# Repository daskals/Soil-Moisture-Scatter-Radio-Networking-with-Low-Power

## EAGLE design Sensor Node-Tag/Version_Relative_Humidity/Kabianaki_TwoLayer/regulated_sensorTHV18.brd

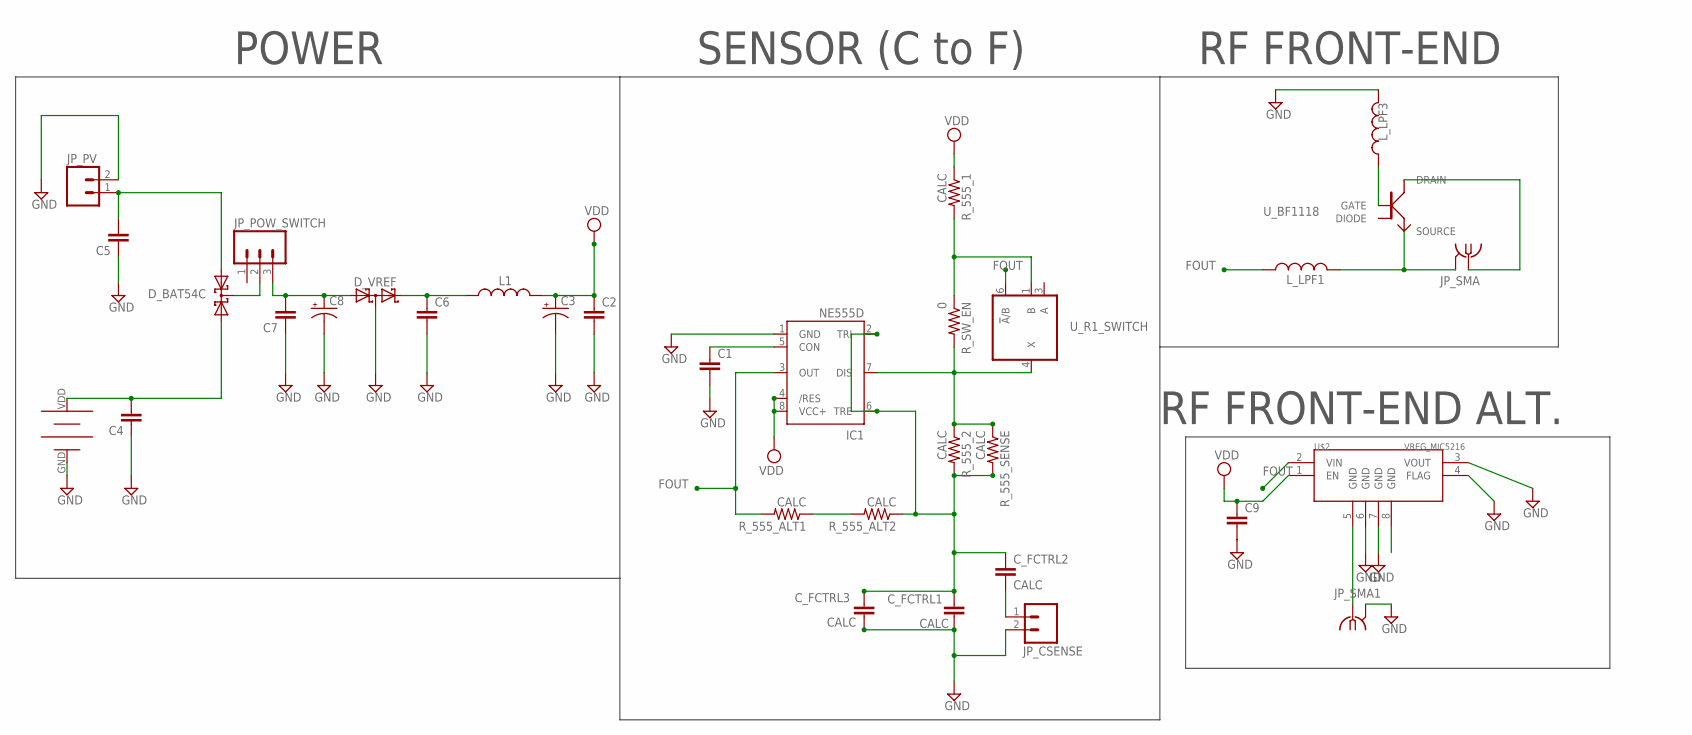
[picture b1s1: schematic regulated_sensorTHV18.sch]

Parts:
C1, C2, C4, C5, C6, C7, C9: CAP0603-CAP; 0603-CAP
C3, C8: CAP_POL1206; EIA3216
C_FCTRL1, C_FCTRL2, C_FCTRL3: CALC; 0603-CAP
D_BAT54C: BAT54C; SOT23
D_VREF: BAT54S; SOT23
IC1: NE555D; SO08
JP_CSENSE: M02LOCK; 1X02_LOCK
JP_POW_SWITCH: M03LOCK; 1X03_LOCK
JP_PV: M02LOCK; 1X02_LOCK
JP_SMA, JP_SMA1: SMA-142-0701-881/886; J502-ND-142-0701-881/886
L1: INDUCTOR0603; 0603
L_LPF1, L_LPF3: INDUCTOR0603; 0603
R_555_1: CALC; 0805
R_555_2, R_555_ALT1, R_555_ALT2, R_555_SENSE: CALC; 0603-RES
R_SW_EN: 0; 0805
U$1: BATTERY_AAA_EAGLE_PLASTIC_DEVICES_DOUBLE; BATTERY-AAA-50MM-DOUBLE
U$2: VREG_MIC5216; MSOP8
U_BF1118: BF1118SOT343R_NXP; SOT343R
U_R1_SWITCH: 741G3157DCKR; DCK_R-PDSO-G6

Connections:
FOUT: IC1.3 (OUT), L_LPF1.1, R_555_ALT1.2, U$2.2 (VIN), U_R1_SWITCH.6 (!A!/B)
GND: C1.2, C2.2, C3.C (-), C4.1, C5.1, C6.2, C7.1, C8.C (-), C9.2, C_FCTRL1.2, C_FCTRL3.2, D_VREF.3 (C1A2), IC1.1 (GND), JP_CSENSE.2, JP_PV.2, JP_SMA1.G@1 (2), JP_SMA1.G@2 (2), JP_SMA1.G@3 (2), JP_SMA1.G@4 (2), L_LPF3.2, U$1.GND, U$2.3 (VOUT), U$2.4 (FLAG), U$2.6 (GND), U$2.7 (GND), U_R1_SWITCH.2 (GND)
unnamed: C5.2, D_BAT54C.1 (A1), JP_PV.1
unnamed: C7.2, C8.A (+), D_VREF.1 (A1), JP_POW_SWITCH.3
unnamed: D_BAT54C.3 (CC), JP_POW_SWITCH.2
unnamed: L_LPF3.1, U_BF1118.1 (GATE)
unnamed: C6.1, D_VREF.2 (C2), L1.1
unnamed: C_FCTRL1.1, C_FCTRL2.1, C_FCTRL3.1, IC1.2 (TRI), IC1.6 (TRE), R_555_2.2, R_555_ALT2.1, R_555_SENSE.2
unnamed: C_FCTRL2.2, JP_CSENSE.1
unnamed: R_555_1.2, R_SW_EN.1, U_R1_SWITCH.1 (B)
unnamed: C1.1, IC1.5 (CON)
unnamed: IC1.7 (DIS), R_555_2.1, R_555_SENSE.1, R_SW_EN.2, U_R1_SWITCH.4 (X)
unnamed: JP_SMA1.1, U$2.5 (GND)
unnamed: C4.2, D_BAT54C.2 (A2), U$1.VDD
unnamed: R_555_ALT1.1, R_555_ALT2.2
RF_FEEDBACK: JP_SMA.G@1 (2), JP_SMA.G@2 (2), JP_SMA.G@3 (2), JP_SMA.G@4 (2), L_LPF1.2, U_BF1118.3 (SOURCE)
RF_IN: JP_SMA.1, U_BF1118.4 (DRAIN)
VDD: C2.1, C3.A (+), C9.1, IC1.4 (/RES), IC1.8 (VCC+), L1.2, R_555_1.1, U$2.1 (EN), U_R1_SWITCH.5 (VCC)

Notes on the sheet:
POWER
SENSOR (C to F)
RF FRONT-END
RF FRONT-END ALT.

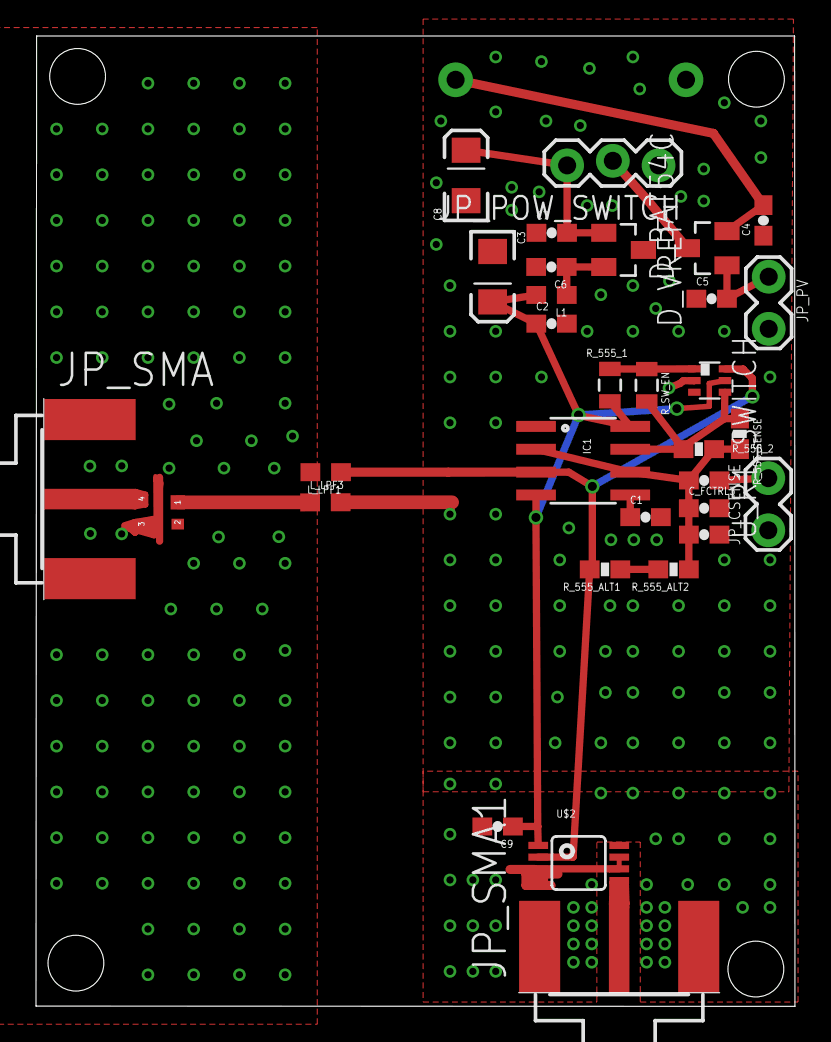
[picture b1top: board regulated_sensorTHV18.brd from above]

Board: 2 copper layers, 42.2 x 53.9 mm, 33 parts (1 on the bottom side), 18 nets.

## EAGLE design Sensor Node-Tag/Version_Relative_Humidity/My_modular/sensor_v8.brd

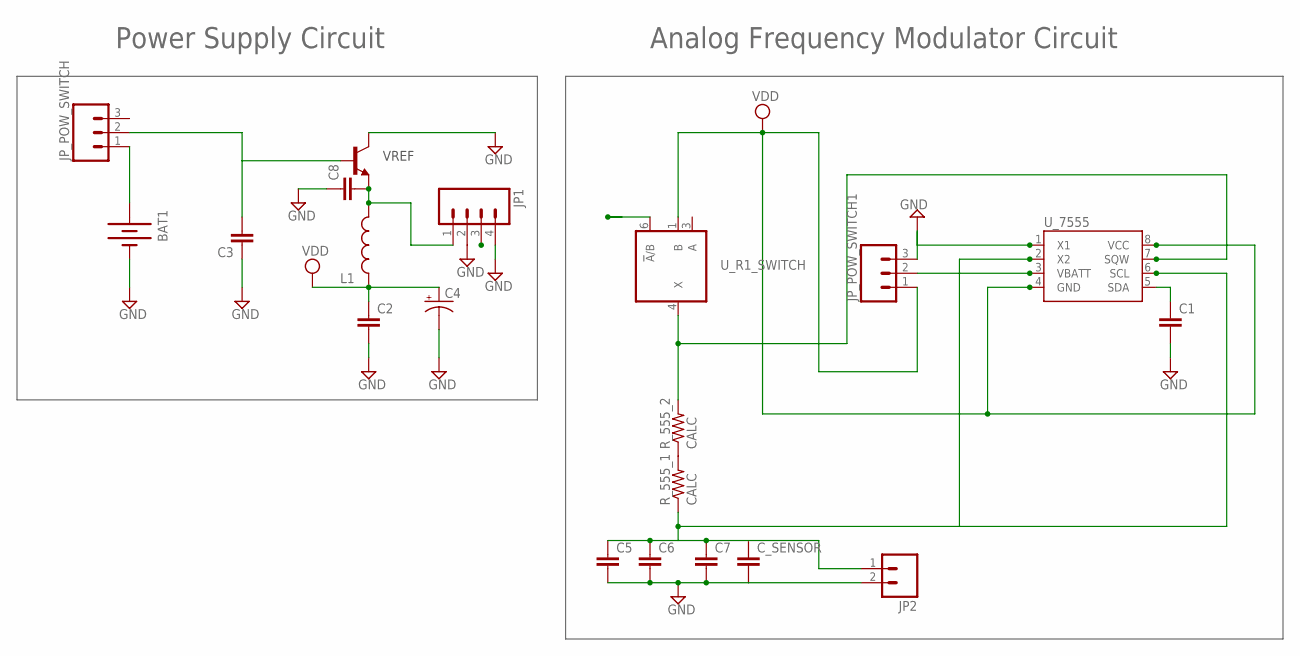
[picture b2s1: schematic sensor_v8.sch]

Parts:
BAT1: BATTERY20PTH_LAB; BATTCOM_20MM_PTH
C1, C2, C3, C8: CAP0603-CAP; 0603-CAP
C4: CAP_POL1206; EIA3216
C5, C6, C7: CAP0805; 0805
C_SENSOR: CAP0805; 0805
JP1: M04LOCK; 1X04_LOCK
JP2: M02PTH; 1X02
JP_POW_SWITCH, JP_POW_SWITCH1: M03LOCK; 1X03_LOCK
L1: INDUCTOR0603; 0603
R_555_1, R_555_2: CALC; 0805
U_7555: DS1307SO8; SO08
U_R1_SWITCH: 741G3157DCKR; DCK_R-PDSO-G6
U_VREF: TRANSISTOR_NPNSOT23-3; SOT23-3

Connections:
FOUT: JP_POW_SWITCH1.2, U_7555.3 (VBATT), U_R1_SWITCH.6 (!A!/B)
GND: BAT1.2 (-), C1.2, C2.2, C3.1, C4.C (-), C5.2, C6.2, C7.2, C8.1, C_SENSOR.2, JP1.2, JP1.4, JP2.2, JP_POW_SWITCH1.3, U_7555.1 (X1), U_R1_SWITCH.2 (GND), U_VREF.3 (C)
unnamed: BAT1.1 (+), JP1.3, JP_POW_SWITCH.1
unnamed: R_555_1.2, R_555_2.1
P2: C5.1, C6.1, C7.1, C_SENSOR.1, JP2.1, R_555_1.1, U_7555.2 (X2), U_7555.6 (SCL)
P5: C1.1, U_7555.5 (SDA)
P7: R_555_2.2, U_7555.7 (SQW), U_R1_SWITCH.4 (X)
VCC: U_R1_SWITCH.5 (VCC)
VDD: C2.1, C4.A (+), JP_POW_SWITCH1.1, L1.1, U_7555.4 (GND), U_7555.8 (VCC), U_R1_SWITCH.1 (B)
VREFIN: C3.2, JP_POW_SWITCH.2, U_VREF.1 (B)
VREFOUT: C8.2, JP1.1, L1.2, U_VREF.2 (E)

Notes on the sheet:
Power Supply Circuit
Analog Frequency Modulator Circuit
VREF

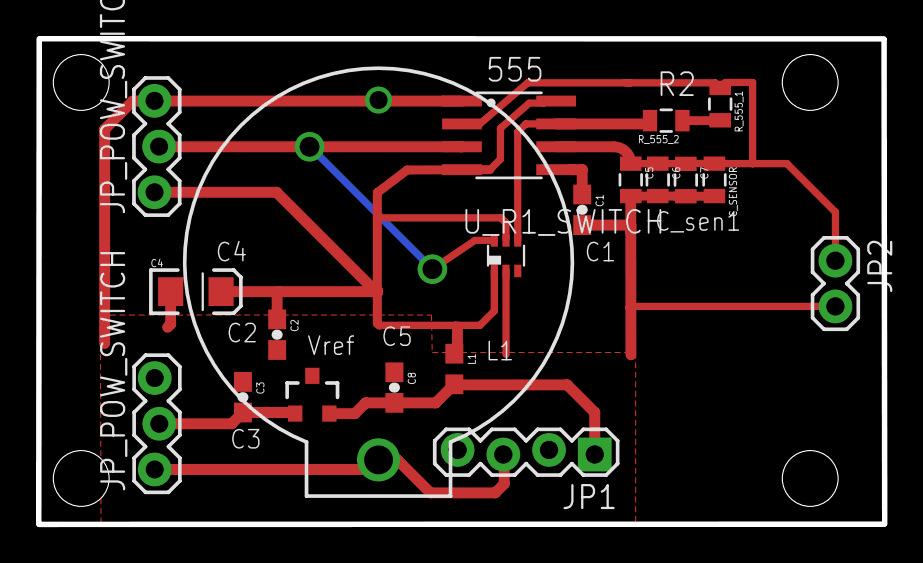
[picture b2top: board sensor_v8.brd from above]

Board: 2 copper layers, 47.0 x 27.0 mm, 20 parts (0 on the bottom side), 10 nets.

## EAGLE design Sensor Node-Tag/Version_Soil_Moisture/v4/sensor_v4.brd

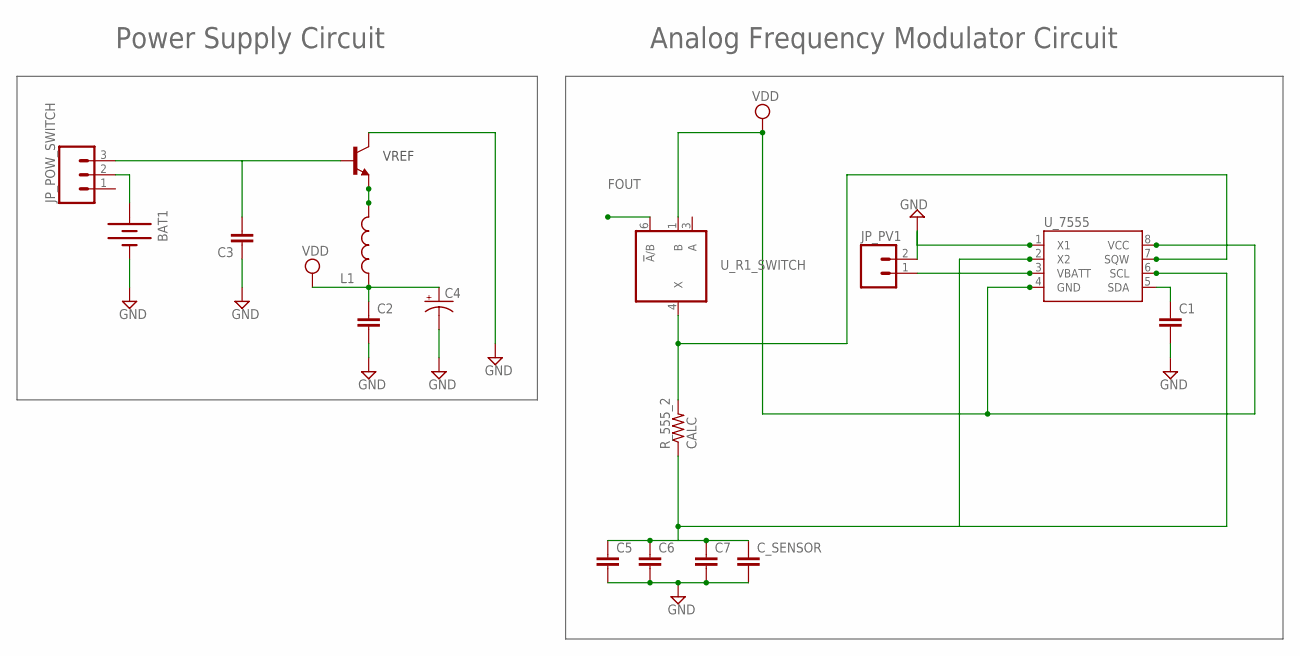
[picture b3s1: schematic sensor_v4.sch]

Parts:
BAT1: BATTERY20PTH_LAB; BATTCOM_20MM_PTH
C1, C2, C3: CAP0603-CAP; 0603-CAP
C4: CAP_POL1206; EIA3216
C5, C6, C7: CAP0805; 0805
C_SENSOR: CAP0805; 0805
JP_POW_SWITCH: M03LOCK; 1X03_LOCK
JP_PV1: M02LOCK; 1X02_LOCK
L1: INDUCTOR0603; 0603
R_555_2: CALC; 0805
U_7555: DS1307SO8; SO08
U_R1_SWITCH: 741G3157DCKR; DCK_R-PDSO-G6
U_VREF: TRANSISTOR_NPNSOT23-3; SOT23-3

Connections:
FOUT: JP_PV1.1, U_7555.3 (VBATT), U_R1_SWITCH.6 (!A!/B)
GND: BAT1.2 (-), C1.2, C2.2, C3.1, C4.C (-), C5.2, C6.2, C7.2, C_SENSOR.2, JP_PV1.2, U_7555.1 (X1), U_R1_SWITCH.2 (GND), U_VREF.3 (C)
unnamed: BAT1.1 (+), JP_POW_SWITCH.2
P2: C5.1, C6.1, C7.1, C_SENSOR.1, R_555_2.1, U_7555.2 (X2), U_7555.6 (SCL)
P5: C1.1, U_7555.5 (SDA)
P7: R_555_2.2, U_7555.7 (SQW), U_R1_SWITCH.4 (X)
VCC: U_R1_SWITCH.5 (VCC)
VDD: C2.1, C4.A (+), L1.1, U_7555.4 (GND), U_7555.8 (VCC), U_R1_SWITCH.1 (B)
VREFIN: C3.2, JP_POW_SWITCH.3, U_VREF.1 (B)
VREFOUT: L1.2, U_VREF.2 (E)

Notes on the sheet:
Power Supply Circuit
Analog Frequency Modulator Circuit
VREF

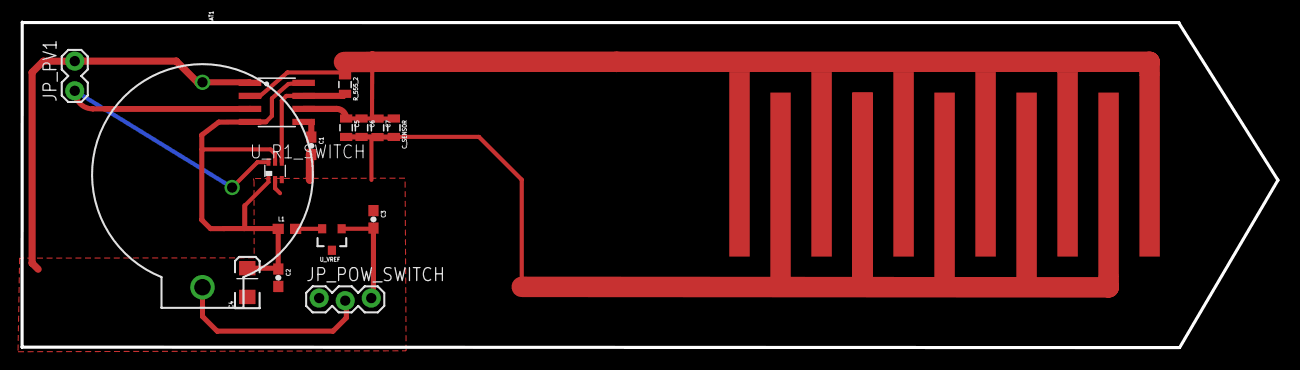
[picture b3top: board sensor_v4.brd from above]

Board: 2 copper layers, 122.5 x 31.8 mm, 16 parts (0 on the bottom side), 9 nets.

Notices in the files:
parts and their libraries:
SparkFun-Resistors: Licensing: CC v3.0 Share-Alike You are welcome to use this library for commercial purposes.
